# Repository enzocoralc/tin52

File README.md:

# tin52
unibody 52-key with rotary encoders that is compatible with 60% cases

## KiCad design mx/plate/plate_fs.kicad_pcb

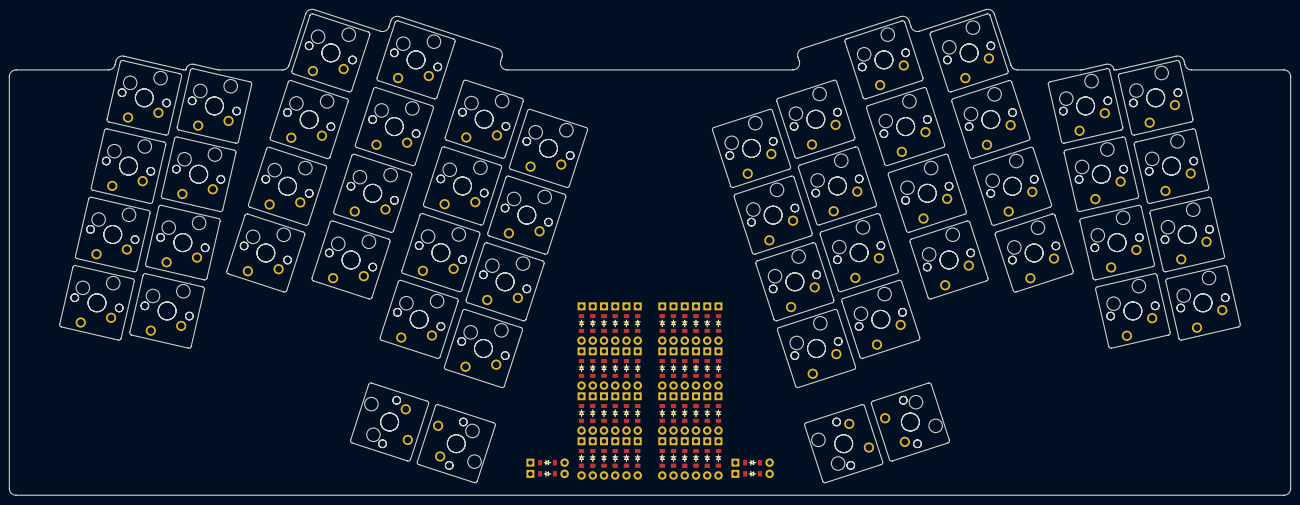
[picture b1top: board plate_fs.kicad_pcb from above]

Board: 2 copper layers, 285.0 x 108.1 mm, 156 parts (0 on the bottom side), 71 nets, no tracks yet.

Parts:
D1, D2, D3, D4, D5, D6, D7, D8, D9, D10, D11, D12, D13, D14, D15, D16, D17, D18, D19, D20, D21, D22, D23, D24, D25, D26, D27, D28, D29, D30, D31, D32, D33, D34, D35, D36, D37, D38, D39, D40, D41, D42, D43, D44, D45, D46, D47, D48, D49, D50, D51, D52: ComboDiode
S1, S2, S3, S4, S5, S6, S7, S8, S9, S10, S11, S12, S13, S14, S15, S16, S17, S18, S19, S20, S21, S22, S23, S24, S25, S26, S27, S28, S29, S30, S31, S32, S33, S34, S35, S36, S37, S38, S39, S40, S41, S42, S43, S44, S45, S46, S47, S48, S49, S50, S51, S52, S53, S54, S55, S56, S57, S58, S59, S60, S61, S62, S63, S64, S65, S66, S67, S68, S69, S70, S71, S72, S73, S74, S75, S76, S77, S78, S79, S80, S81, S82, S83, S84, S85, S86, S87, S88, S89, S90, S91, S92, S93, S94, S95, S96, S97, S98, S99, S100, S101, S102, S103, S104: MX

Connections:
P0: S9.1, S10.1, S11.1, S12.1, S13.1, S14.1, S15.1, S16.1
P1: S1.1, S2.1, S3.1, S4.1, S5.1, S6.1, S7.1, S8.1
P2: S17.1, S18.1, S19.1, S20.1, S21.1, S22.1, S23.1, S24.1
P3: S25.1, S26.1, S27.1, S28.1, S29.1, S30.1, S31.1, S32.1
P4: S33.1, S34.1, S35.1, S36.1, S37.1, S38.1, S39.1, S40.1, S49.1, S50.1
P5: S41.1, S42.1, S43.1, S44.1, S45.1, S46.1, S47.1, S48.1, S51.1, S52.1
P6: D1.1, D1.2, D5.1, D5.2, D9.1, D9.2, D13.1, D13.2, D17.1, D17.2, D21.1, D21.2, D27.1, D27.2, D31.1, D31.2, D35.1, D35.2, D39.1, D39.2, D43.1, D43.2, D47.1, D47.2
P7: D2.1, D2.2, D6.1, D6.2, D10.1, D10.2, D14.1, D14.2, D18.1, D18.2, D22.1, D22.2, D28.1, D28.2, D32.1, D32.2, D36.1, D36.2, D40.1, D40.2, D44.1, D44.2, D48.1, D48.2
P8: D3.1, D3.2, D7.1, D7.2, D11.1, D11.2, D15.1, D15.2, D19.1, D19.2, D23.1, D23.2, D29.1, D29.2, D33.1, D33.2, D37.1, D37.2, D41.1, D41.2, D45.1, D45.2, D49.1, D49.2
P9: D4.1, D4.2, D8.1, D8.2, D12.1, D12.2, D16.1, D16.2, D20.1, D20.2, D24.1, D24.2, D30.1, D30.2, D34.1, D34.2, D38.1, D38.2, D42.1, D42.2, D46.1, D46.2, D50.1, D50.2
P10: D25.1, D25.2, D26.1, D26.2, D51.1, D51.2, D52.1, D52.2
P14: S93.1, S94.1, S95.1, S96.1, S97.1, S98.1, S99.1, S100.1, S103.1, S104.1
P15: S85.1, S86.1, S87.1, S88.1, S89.1, S90.1, S91.1, S92.1, S101.1, S102.1
P18: S77.1, S78.1, S79.1, S80.1, S81.1, S82.1, S83.1, S84.1
P19: S69.1, S70.1, S71.1, S72.1, S73.1, S74.1, S75.1, S76.1
P20: S61.1, S62.1, S63.1, S64.1, S65.1, S66.1, S67.1, S68.1
P21: S53.1, S54.1, S55.1, S56.1, S57.1, S58.1, S59.1, S60.1
index_bottom: D17.1, D17.2, S33.2, S34.2
index_home: D18.1, D18.2, S35.2, S36.2
index_num: D20.1, D20.2, S39.2, S40.2
index_thumb: D25.1, D25.2
index_top: D19.1, D19.2, S37.2, S38.2
inner_bottom: D21.1, D21.2, S41.2, S42.2
inner_home: D22.1, D22.2, S43.2, S44.2
inner_num: D24.1, D24.2, S47.2, S48.2
inner_thumb: D26.1, D26.2, S51.2, S52.2
inner_top: D23.1, D23.2, S45.2, S46.2
middle_bottom: D13.1, D13.2, S25.2, S26.2
middle_home: D14.1, D14.2, S27.2, S28.2
middle_num: D16.1, D16.2, S31.2, S32.2
middle_top: D15.1, D15.2, S29.2, S30.2
mirror_index_bottom: D43.1, D43.2, S85.2, S86.2
mirror_index_home: D44.1, D44.2, S87.2, S88.2
mirror_index_num: D46.1, D46.2, S91.2, S92.2
mirror_index_thumb: D51.1, D51.2
mirror_index_top: D45.1, D45.2, S89.2, S90.2
mirror_inner_bottom: D47.1, D47.2, S93.2, S94.2
mirror_inner_home: D48.1, D48.2, S95.2, S96.2
mirror_inner_num: D50.1, D50.2, S99.2, S100.2
mirror_inner_thumb: D52.1, D52.2, S103.2, S104.2
mirror_inner_top: D49.1, D49.2, S97.2, S98.2
mirror_middle_bottom: D39.1, D39.2, S77.2, S78.2
mirror_middle_home: D40.1, D40.2, S79.2, S80.2
mirror_middle_num: D42.1, D42.2, S83.2, S84.2
mirror_middle_top: D41.1, D41.2, S81.2, S82.2
mirror_outer_bottom: D27.1, D27.2, S53.2, S54.2
mirror_outer_home: D28.1, D28.2, S55.2, S56.2
mirror_outer_num: D30.1, D30.2, S59.2, S60.2
mirror_outer_thumb: S101.2, S102.2
mirror_outer_top: D29.1, D29.2, S57.2, S58.2
mirror_pinky_bottom: D31.1, D31.2, S61.2, S62.2
mirror_pinky_home: D32.1, D32.2, S63.2, S64.2
mirror_pinky_num: D34.1, D34.2, S67.2, S68.2
mirror_pinky_top: D33.1, D33.2, S65.2, S66.2
mirror_ring_bottom: D35.1, D35.2, S69.2, S70.2
mirror_ring_home: D36.1, D36.2, S71.2, S72.2
mirror_ring_num: D38.1, D38.2, S75.2, S76.2
mirror_ring_top: D37.1, D37.2, S73.2, S74.2
outer_bottom: D1.1, D1.2, S1.2, S2.2
outer_home: D2.1, D2.2, S3.2, S4.2
outer_num: D4.1, D4.2, S7.2, S8.2
outer_thumb: S49.2, S50.2
outer_top: D3.1, D3.2, S5.2, S6.2
pinky_bottom: D5.1, D5.2, S9.2, S10.2
pinky_home: D6.1, D6.2, S11.2, S12.2
pinky_num: D8.1, D8.2, S15.2, S16.2
pinky_top: D7.1, D7.2, S13.2, S14.2
ring_bottom: D9.1, D9.2, S17.2, S18.2
ring_home: D10.1, D10.2, S19.2, S20.2
ring_num: D12.1, D12.2, S23.2, S24.2
ring_top: D11.1, D11.2, S21.2, S22.2

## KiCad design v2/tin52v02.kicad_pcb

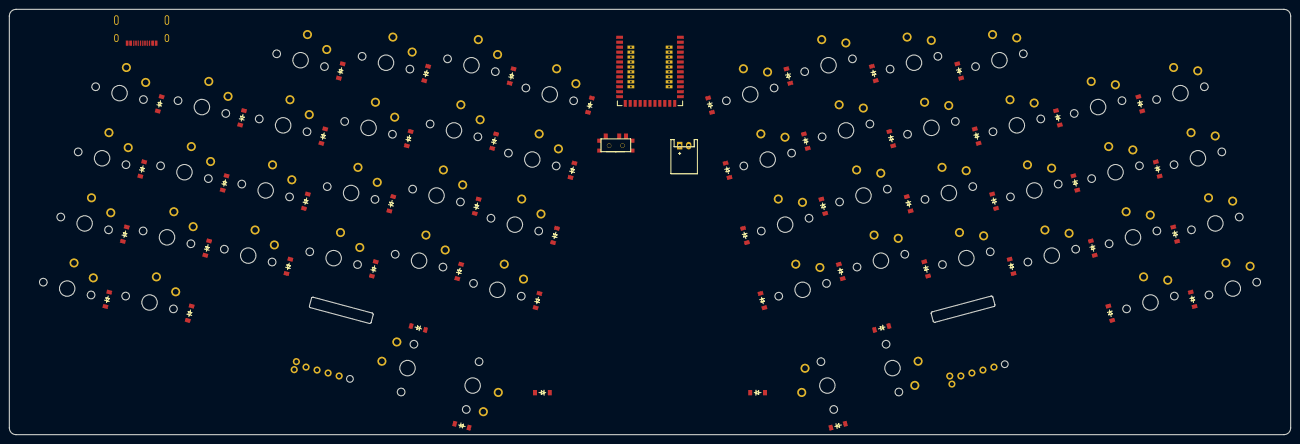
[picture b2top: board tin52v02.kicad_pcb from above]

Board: 2 copper layers, 285.0 x 94.6 mm, 110 parts (0 on the bottom side), 74 nets, no tracks yet.

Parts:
B1: SW_TACT_ALPS_SKQGABE010
D1, D2, D3, D4, D5, D6, D7, D8, D9, D10, D11, D12, D13, D14, D15, D16, D17, D18, D19, D20, D21, D22, D23, D24, D25, D26, D27, D28, D29, D30, D31, D32, D33, D34, D35, D36, D37, D38, D39, D40, D41, D42, D43, D44, D45, D46, D47, D48, D49, D50, D51, D52, D53, D54: ComboDiode
JST1: JST_PH_S2B-PH-K_02x2.00mm_Angled
S1, S2, S3, S4, S5, S6, S7, S8, S9, S10, S11, S12, S13, S14, S15, S16, S17, S18, S19, S20, S21, S22, S23, S24, S25, S26, S27, S28, S29, S30, S31, S32, S33, S34, S35, S36, S37, S38, S39, S40, S41, S42, S43, S44, S45, S46, S47, S48, S49, S50, S51, S52: PG1350
T1: SPDT_C128955
USB1: USB-C-12-Pin-MidMount

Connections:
DN: USB1.6, USB1.8
DP: USB1.5, USB1.7
GND: B1.2, T1.2, USB1.1, USB1.12, USB1.13
P0: S5.1, S6.1, S7.1, S8.1
P1: S1.1, S2.1, S3.1, S4.1
P2: S9.1, S10.1, S11.1, S12.1
P3: S13.1, S14.1, S15.1, S16.1
P4: S17.1, S18.1, S19.1, S20.1, S25.1
P5: S21.1, S22.1, S23.1, S24.1, S26.1
P6: D4.1, D8.1, D12.1, D16.1, D20.1, D24.1, D30.1, D34.1, D38.1, D42.1, D46.1, D50.1
P7: D3.1, D7.1, D11.1, D15.1, D19.1, D23.1, D29.1, D33.1, D37.1, D41.1, D45.1, D49.1, D53.1, D54.1
P8: D2.1, D6.1, D10.1, D14.1, D18.1, D22.1, D28.1, D32.1, D36.1, D40.1, D44.1, D48.1
P9: D1.1, D5.1, D9.1, D13.1, D17.1, D21.1, D27.1, D31.1, D35.1, D39.1, D43.1, D47.1
P10: D25.1, D26.1, D51.1, D52.1
P14: S47.1, S48.1, S49.1, S50.1, S52.1
P15: S43.1, S44.1, S45.1, S46.1, S51.1
P18: S39.1, S40.1, S41.1, S42.1
P19: S35.1, S36.1, S37.1, S38.1
P20: S31.1, S32.1, S33.1, S34.1
P21: S27.1, S28.1, S29.1, S30.1
VBUS: USB1.2, USB1.11
enc_diode: D53.2, D54.2
index_bottom: D17.2, S17.2
index_home: D18.2, S18.2
index_num: D20.2, S20.2
index_top: D19.2, S19.2
inner_bottom: D21.2, S21.2
inner_home: D22.2, S22.2
inner_num: D24.2, S24.2
inner_thumb: D26.2, S26.2
inner_top: D23.2, S23.2
middle_bottom: D13.2, S13.2
middle_home: D14.2, S14.2
middle_num: D16.2, S16.2
middle_top: D15.2, S15.2
mirror_index_bottom: D43.2, S43.2
mirror_index_home: D44.2, S44.2
mirror_index_num: D46.2, S46.2
mirror_index_top: D45.2, S45.2
mirror_inner_bottom: D47.2, S47.2
mirror_inner_home: D48.2, S48.2
mirror_inner_num: D50.2, S50.2
mirror_inner_thumb: D52.2, S52.2
mirror_inner_top: D49.2, S49.2
mirror_middle_bottom: D39.2, S39.2
mirror_middle_home: D40.2, S40.2
mirror_middle_num: D42.2, S42.2
mirror_middle_top: D41.2, S41.2
mirror_outer_bottom: D27.2, S27.2
mirror_outer_home: D28.2, S28.2
mirror_outer_num: D30.2, S30.2
mirror_outer_thumb: D51.2, S51.2
mirror_outer_top: D29.2, S29.2
mirror_pinky_bottom: D31.2, S31.2
mirror_pinky_home: D32.2, S32.2
mirror_pinky_num: D34.2, S34.2
mirror_pinky_top: D33.2, S33.2
mirror_ring_bottom: D35.2, S35.2
mirror_ring_home: D36.2, S36.2
mirror_ring_num: D38.2, S38.2
mirror_ring_top: D37.2, S37.2
outer_bottom: D1.2, S1.2
outer_home: D2.2, S2.2
outer_num: D4.2, S4.2
outer_thumb: D25.2, S25.2
outer_top: D3.2, S3.2
pinky_bottom: D5.2, S5.2
pinky_home: D6.2, S6.2
pinky_num: D8.2, S8.2
pinky_top: D7.2, S7.2
ring_bottom: D9.2, S9.2
ring_home: D10.2, S10.2
ring_num: D12.2, S12.2
ring_top: D11.2, S11.2

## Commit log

2022-02-01 added the ergogen files as well as kicad projects
2022-02-04 added mx version and some variations, new power switch
2022-02-05 added plate stuff for mx
2022-02-05 added plate pcb to ergogen file
2022-02-07 added some experimentation with pm pcb and plate
2022-02-09 added some tests stuff
2022-02-09 ergogen file changed
